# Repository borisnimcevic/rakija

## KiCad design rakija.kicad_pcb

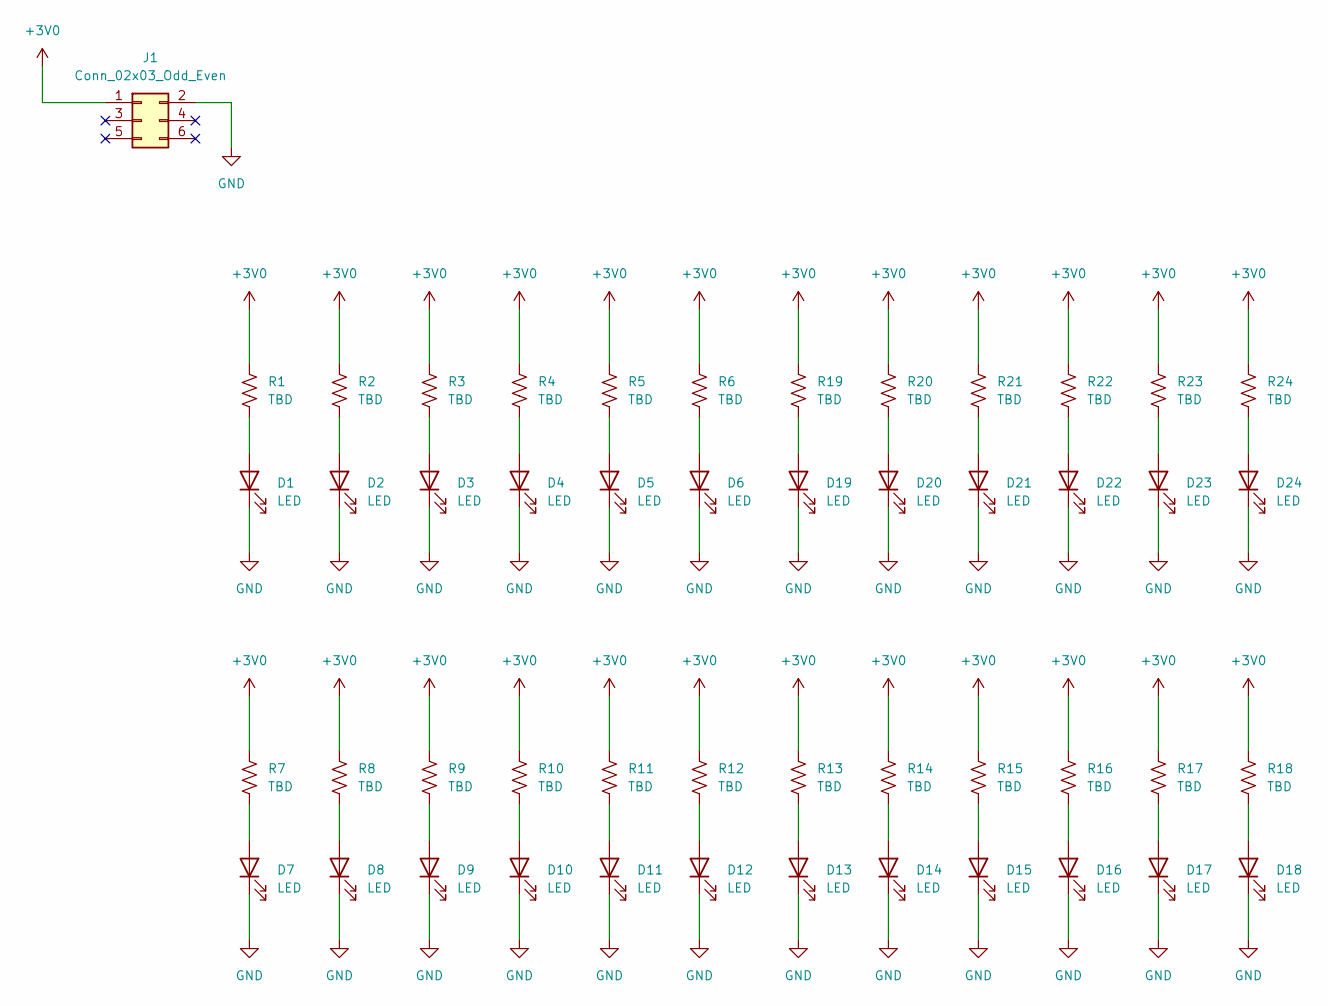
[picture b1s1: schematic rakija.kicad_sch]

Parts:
D1, D2, D3, D4, D5, D6, D7, D8, D9, D10, D11, D12, D13, D14, D15, D16, D17, D18, D19, D20, D21, D22, D23, D24: LED; LED_0603_1608Metric_Pad1.05x0.95mm_HandSolder
J1: Conn_02x03_Odd_Even; IDC-Header_2x03_P2.54mm_Vertical_SMD
R1, R2, R3, R4, R5, R6, R7, R8, R9, R10, R11, R12, R13, R14, R15, R16, R17, R18, R19, R20, R21, R22, R23, R24: TBD; R_0603_1608Metric_Pad0.98x0.95mm_HandSolder

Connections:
+3V0: J1.1, R1.1, R2.1, R3.1, R4.1, R5.1, R6.1, R7.1, R8.1, R9.1, R10.1, R11.1, R12.1, R13.1, R14.1, R15.1, R16.1, R17.1, R18.1, R19.1, R20.1, R21.1, R22.1, R23.1, R24.1
GND: D1.1 (K), D2.1 (K), D3.1 (K), D4.1 (K), D5.1 (K), D6.1 (K), D7.1 (K), D8.1 (K), D9.1 (K), D10.1 (K), D11.1 (K), D12.1 (K), D13.1 (K), D14.1 (K), D15.1 (K), D16.1 (K), D17.1 (K), D18.1 (K), D19.1 (K), D20.1 (K), D21.1 (K), D22.1 (K), D23.1 (K), D24.1 (K), J1.2
unnamed: D1.2 (A), R1.2
unnamed: D2.2 (A), R2.2
unnamed: D3.2 (A), R3.2
unnamed: D4.2 (A), R4.2
unnamed: D5.2 (A), R5.2
unnamed: D6.2 (A), R6.2
unnamed: D7.2 (A), R7.2
unnamed: D8.2 (A), R8.2
unnamed: D9.2 (A), R9.2
unnamed: D10.2 (A), R10.2
unnamed: D11.2 (A), R11.2
unnamed: D12.2 (A), R12.2
unnamed: D13.2 (A), R13.2
unnamed: D14.2 (A), R14.2
unnamed: D15.2 (A), R15.2
unnamed: D16.2 (A), R16.2
unnamed: D17.2 (A), R17.2
unnamed: D18.2 (A), R18.2
unnamed: D19.2 (A), R19.2
unnamed: D20.2 (A), R20.2
unnamed: D21.2 (A), R21.2
unnamed: D22.2 (A), R22.2
unnamed: D23.2 (A), R23.2
unnamed: D24.2 (A), R24.2

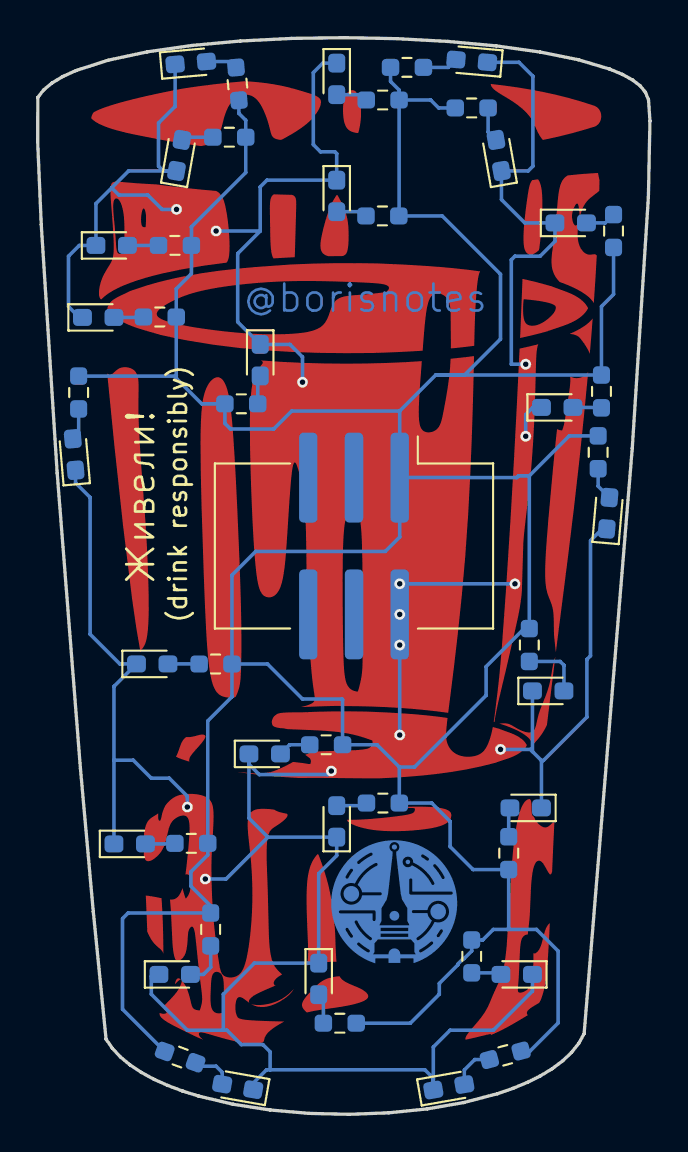
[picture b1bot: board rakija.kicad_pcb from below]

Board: 2 copper layers, 34.0 x 59.8 mm, 49 parts (49 on the bottom side), 26 nets.

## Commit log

2026-04-24 init rakija PCB
2026-04-24 init kicad rakija project
2026-04-24 edge and silk layer down
2026-04-24 main graphics done
2026-04-24 added some components
2026-04-25 leds routed
2026-04-25 ready for gerber
2026-04-25 fabrication files
